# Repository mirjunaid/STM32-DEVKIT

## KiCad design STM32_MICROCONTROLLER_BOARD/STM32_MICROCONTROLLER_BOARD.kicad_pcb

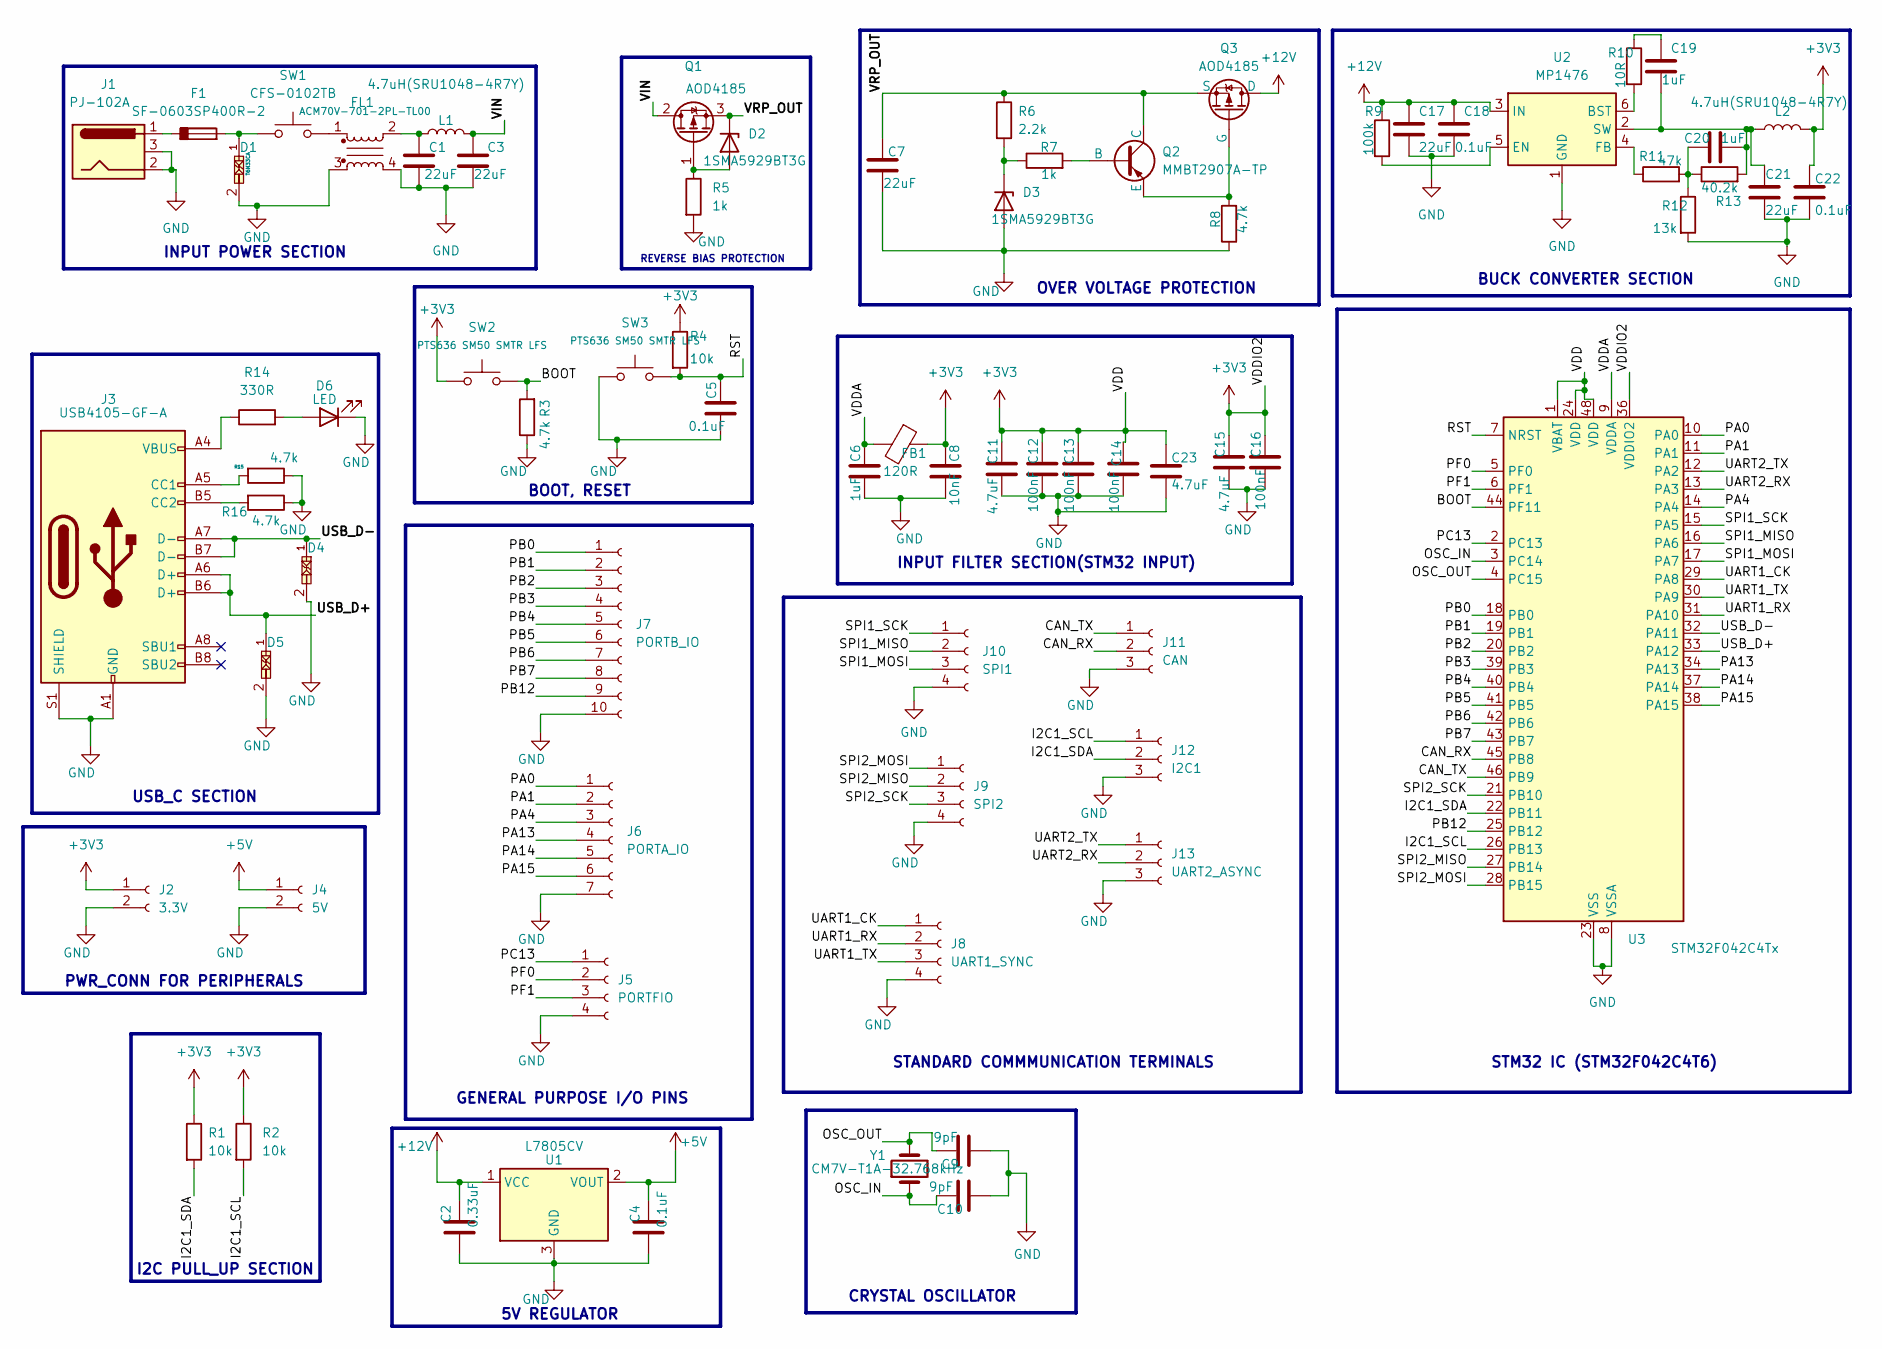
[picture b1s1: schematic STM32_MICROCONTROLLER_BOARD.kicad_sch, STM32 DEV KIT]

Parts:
C1, C3, C7, C17, C21: 22uF; C_0603_1608Metric
C2: 0.33uF; C_0603_1608Metric
C4, C5, C18, C22: 0.1uF; C_0603_1608Metric
C6, C19, C20: 1uF; C_0603_1608Metric
C8: 10nF; C_0603_1608Metric
C9, C10: 9pF; C_0603_1608Metric
C11, C15, C23: 4.7uF; C_0603_1608Metric
C12, C13, C14, C16: 100nF; C_0603_1608Metric
D1: T6N33CA; Vishay_SMPA
D2, D3: 1SMA5929BT3G; D_SMB
D4, D5: T6N33CA; tvs_diode_footprint
D6: LED; LED_0201_0603Metric
F1: SF-0603SP400R-2; Fuse_0603_1608Metric_Pad1.05x0.95mm_HandSolder
FB1: 120R; Fuse_0805_2012Metric
FL1: ACM70V-701-2PL-TL00; L_CommonModeChoke_TDK_ACM7060
J1: PJ-102A; BarrelJack_Horizontal
J2: 3.3V; JST_EH_B2B-EH-A_1x02_P2.50mm_Vertical
J3: USB4105-GF-A; USB_C_Receptacle_GCT_USB4105-xx-A_16P_TopMnt_Horizontal
J4: 5V; JST_EH_B2B-EH-A_1x02_P2.50mm_Vertical
J5: PORTFIO; PinHeader_1x04_P2.54mm_Vertical
J6: PORTA_IO; PinHeader_1x07_P2.54mm_Vertical_SMD_Pin1Left
J7: PORTB_IO; PinHeader_1x10_P2.54mm_Vertical
J8: UART1_SYNC; JST_PH_B4B-PH-K_1x04_P2.00mm_Vertical
J9: SPI2; JST_PH_B4B-PH-K_1x04_P2.00mm_Vertical
J10: SPI1; JST_PH_B4B-PH-K_1x04_P2.00mm_Vertical
J11: CAN; JST_PH_B3B-PH-K_1x03_P2.00mm_Vertical
J12: I2C1; JST_PH_B3B-PH-K_1x03_P2.00mm_Vertical
J13: UART2_ASYNC; JST_PH_B3B-PH-K_1x03_P2.00mm_Vertical
L1, L2: 4.7uH(SRU1048-4R7Y); L_Bourns-SRU1028_10.0x10.0mm
Q1, Q3: AOD4185; TO252_AOS-M
Q2: MMBT2907A-TP; SOT-23-3
R1, R2, R4: 10k; R_0603_1608Metric
R3, R8, R15, R16: 4.7k; R_0603_1608Metric
R5, R7: 1k; R_0603_1608Metric
R6: 2.2k; R_0603_1608Metric
R9: 100k; R_0603_1608Metric
R10: 10R; R_0603_1608Metric
R11: 47k; R_0603_1608Metric
R12: 13k; R_0603_1608Metric
R13: 40.2k; R_0603_1608Metric
R14: 330R; LED_0201_0603Metric
SW1: CFS-0102TB; SW_Tactile_SPST_NO_Straight_CK_PTS636Sx25SMTRLFS
SW2, SW3: PTS636 SM50 SMTR LFS; SW_Tactile_SPST_NO_Straight_CK_PTS636Sx25SMTRLFS
U1: L7805CV; TO252_AOS
U2: MP1476; TSOT-23-6
U3: STM32F042C4Tx; LQFP-48_7x7mm_P0.5mm
Y1: CM7V-T1A-32.768kHz; XTAL_CM7V-T1A-32.768KHZ-12.5PF-100PPM-TB-QC

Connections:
+3V3: C8.1, C11.1, C12.2, C13.2, C14.2, C15.2, C16.2, C22.1, C23.1, FB1.1, J2.1, L2.2, R1.1, R2.1, R4.1, SW2.1, U3.1 (VBAT), U3.24 (VDD), U3.36 (VDDIO2), U3.48 (VDD)
+5V: C4.2, J4.1, U1.2 (VOUT)
+12V: C2.2, C17.1, C18.1, Q3.1 (D), R9.1, U1.1 (VCC), U2.3 (IN)
/BOOT: R3.2, SW2.2, U3.44 (PF11)
/CAN_RX: J11.2, U3.45 (PB8)
/CAN_TX: J11.1, U3.46 (PB9)
/I2C1_SCL: J12.1, R2.2, U3.26 (PB13)
/I2C1_SDA: J12.2, R1.2, U3.22 (PB11)
/OSC_IN: C10.2, U3.3 (PC14), Y1.1
/OSC_OUT: C9.2, U3.4 (PC15), Y1.2
/PA0: J6.1, U3.10 (PA0)
/PA1: J6.2, U3.11 (PA1)
/PA4: J6.3, U3.14 (PA4)
/PA13: J6.4, U3.34 (PA13)
/PA14: J6.5, U3.37 (PA14)
/PA15: J6.6, U3.38 (PA15)
/PB0: J7.1, U3.18 (PB0)
/PB1: J7.2, U3.19 (PB1)
/PB2: J7.3, U3.20 (PB2)
/PB3: J7.4, U3.39 (PB3)
/PB4: J7.5, U3.40 (PB4)
/PB5: J7.6, U3.41 (PB5)
/PB6: J7.7, U3.42 (PB6)
/PB7: J7.8, U3.43 (PB7)
/PB12: J7.9, U3.25 (PB12)
/PC13: J5.1, U3.2 (PC13)
/PF0: J5.2, U3.5 (PF0)
/PF1: J5.3, U3.6 (PF1)
/RST: C5.2, R4.2, SW3.2, U3.7 (NRST)
/SPI1_MISO: J10.2, U3.16 (PA6)
/SPI1_MOSI: J10.3, U3.17 (PA7)
/SPI1_SCK: J10.1, U3.15 (PA5)
/SPI2_MISO: J9.2, U3.27 (PB14)
/SPI2_MOSI: J9.1, U3.28 (PB15)
/SPI2_SCK: J9.3, U3.21 (PB10)
/UART1_CK: J8.1, U3.29 (PA8)
/UART1_RX: J8.2, U3.31 (PA10)
/UART1_TX: J8.3, U3.30 (PA9)
/UART2_RX: J13.2, U3.13 (PA3)
/UART2_TX: J13.1, U3.12 (PA2)
/USB_D+: D5.1, J3.A6 (D+), J3.B6 (D+), U3.33 (PA12)
/USB_D-: D4.1, J3.A7 (D-), J3.B7 (D-), U3.32 (PA11)
/VDDA: C6.1, FB1.2, U3.9 (VDDA)
/VIN: C3.1, L1.2, Q1.2 (D)
/VRP_OUT: C7.1, D2.1 (K), Q1.3 (S), Q2.1 (C), Q3.3 (S), R6.1
GND: C1.2, C2.1, C3.2, C4.1, C5.1, C6.2, C7.2, C8.2, C9.1, C10.1, C11.2, C12.1, C13.1, C14.1, C15.1, C16.1, C17.2, C18.2, C21.2, C22.2, C23.2, D1.2, D3.2 (A), D4.2, D5.2, D6.1 (K), FL1.3, FL1.4, J1.2, J1.3, J2.2, J3.A1 (GND), J3.A12 (GND), J3.B1 (GND), J3.B12 (GND), J3.S1 (SHIELD), J4.2, J5.4, J6.7, J7.10, J8.4, J9.4, J10.4, J11.3, J12.3, J13.3, R3.1, R5.2, R8.1, R12.2, R15.1, R16.1, SW3.1, U1.3 (GND), U2.1 (GND), U3.8 (VSSA), U3.23 (VSS), U3.35 (VSS), U3.47 (VSS)
unnamed: C1.1, FL1.2, L1.1
unnamed: C19.1, R10.1
unnamed: C20.1, R11.2, R12.1, R13.1
unnamed: D1.1, F1.2, SW1.1
unnamed: D2.2 (A), Q1.1 (G), R5.1
unnamed: D3.1 (K), R6.2, R7.1
unnamed: D6.2 (A), R14.2
unnamed: F1.1, J1.1
unnamed: FL1.1, SW1.2
unnamed: J3.A5 (CC1), R15.2
unnamed: J3.B5 (CC2), R16.2
unnamed: J3.A4 (VBUS), J3.A9 (VBUS), J3.B4 (VBUS), J3.B9 (VBUS), R14.1
unnamed: Q2.2 (B), R7.2
unnamed: Q2.3 (E), Q3.2 (G), R8.2
unnamed: R10.2, U2.6 (BST)
unnamed: R9.2, U2.5 (EN)
unnamed: R11.1, U2.4 (FB)
unnamed: C19.2, C20.2, C21.1, L2.1, R13.2, U2.2 (SW)

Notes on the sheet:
CRYSTAL OSCILLATOR
OVER VOLTAGE PROTECTION
STANDARD COMMMUNICATION TERMINALS
REVERSE BIAS PROTECTION
BOOT, RESET
BUCK CONVERTER SECTION
INPUT POWER SECTION
5V REGULATOR
INPUT FILTER SECTION(STM32 INPUT)
PWR_CONN FOR PERIPHERALS
I2C PULL_UP SECTION
GENERAL PURPOSE I/O PINS
STM32 IC (STM32F042C4T6)
USB_C SECTION

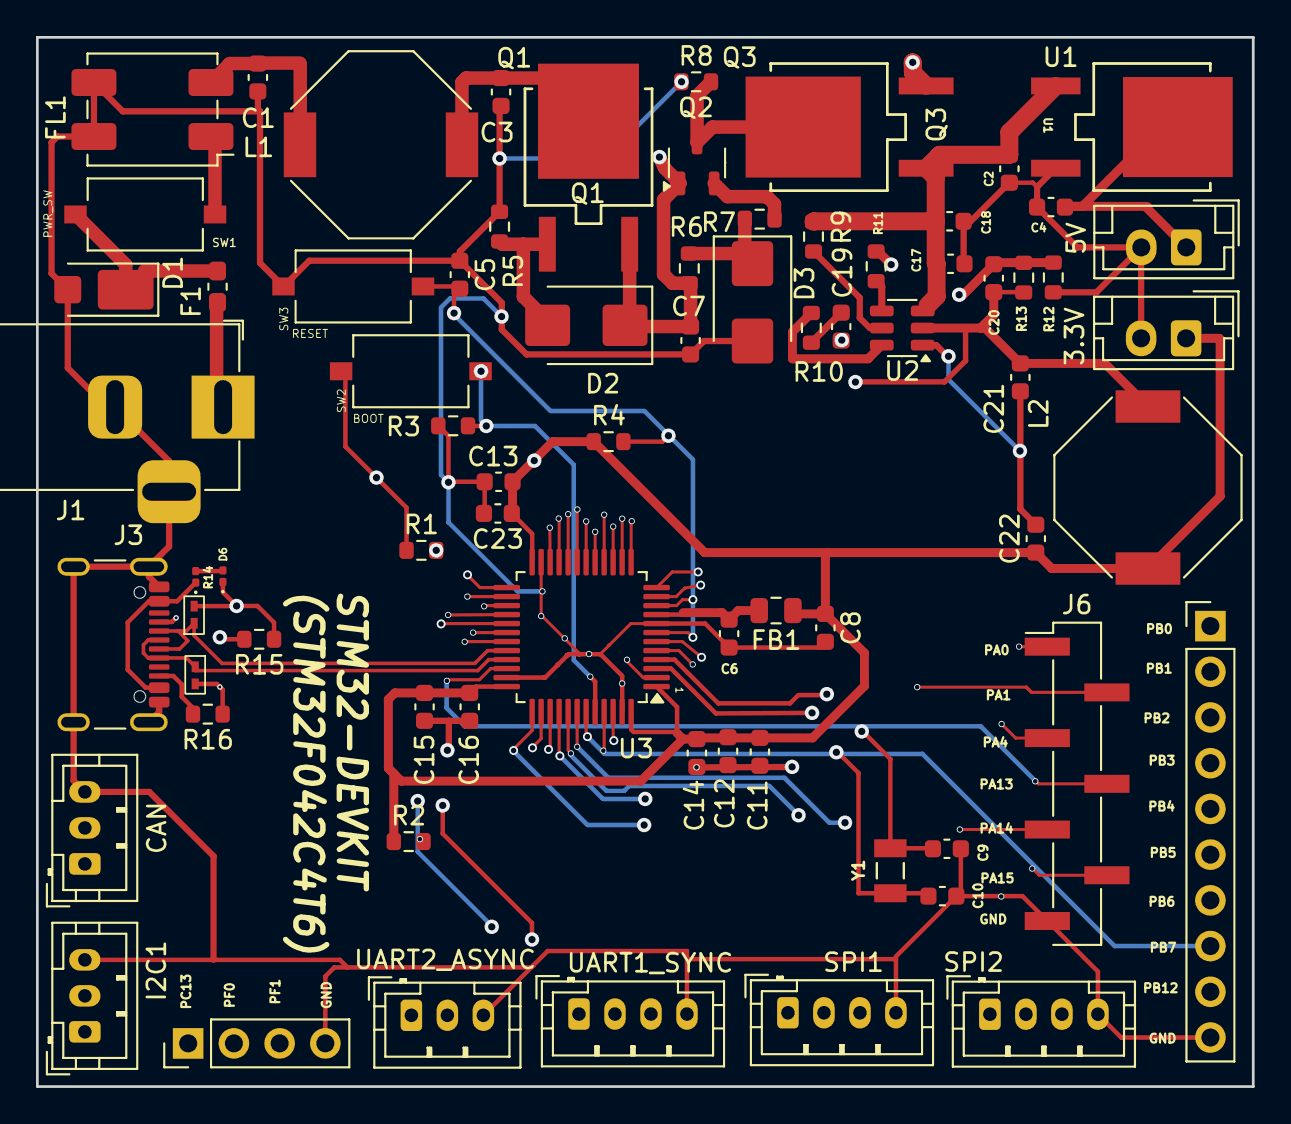
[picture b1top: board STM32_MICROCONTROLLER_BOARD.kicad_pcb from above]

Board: 4 copper layers, 67.5 x 58.3 mm, 73 parts (0 on the bottom side), 64 nets.

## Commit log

2024-04-13 first commit
    The project files are uploaded into the github repo created on github manually with a readme.md file.....
2024-04-13 Delete STM32_MICROCONTROLLER_BOARD/output/stm32_pcb.png
    pcb pic needed to be replaced...
2024-04-13 new pcb image
    The previous image had warning markers thats why I replaced that with this new image..
